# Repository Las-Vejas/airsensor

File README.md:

# かぜ (kaze)

A surrounding sensor that measures a bunch of things!
Heres a list of what it can measure:
 - Temperature (BME680)
 - Humidity (BME680)
 - Pressure (BME680)
 - CO<sub>2</sub> (BME680) (therefore AQI too)
 - lux (TSL2561)
 - and a couple more...

It is powered by the ESP32-C6 module and supports IoT protocols like Zigbee, Wi-fi, Bluetooth and Thread.
The software (that I will eventually write) will be for ESPHome as its very easy to set up IoT and home devices that way with the help of Home Assistant.

The biggest cost for this project would be the BME680 sensor as it costs about 10$

## Images

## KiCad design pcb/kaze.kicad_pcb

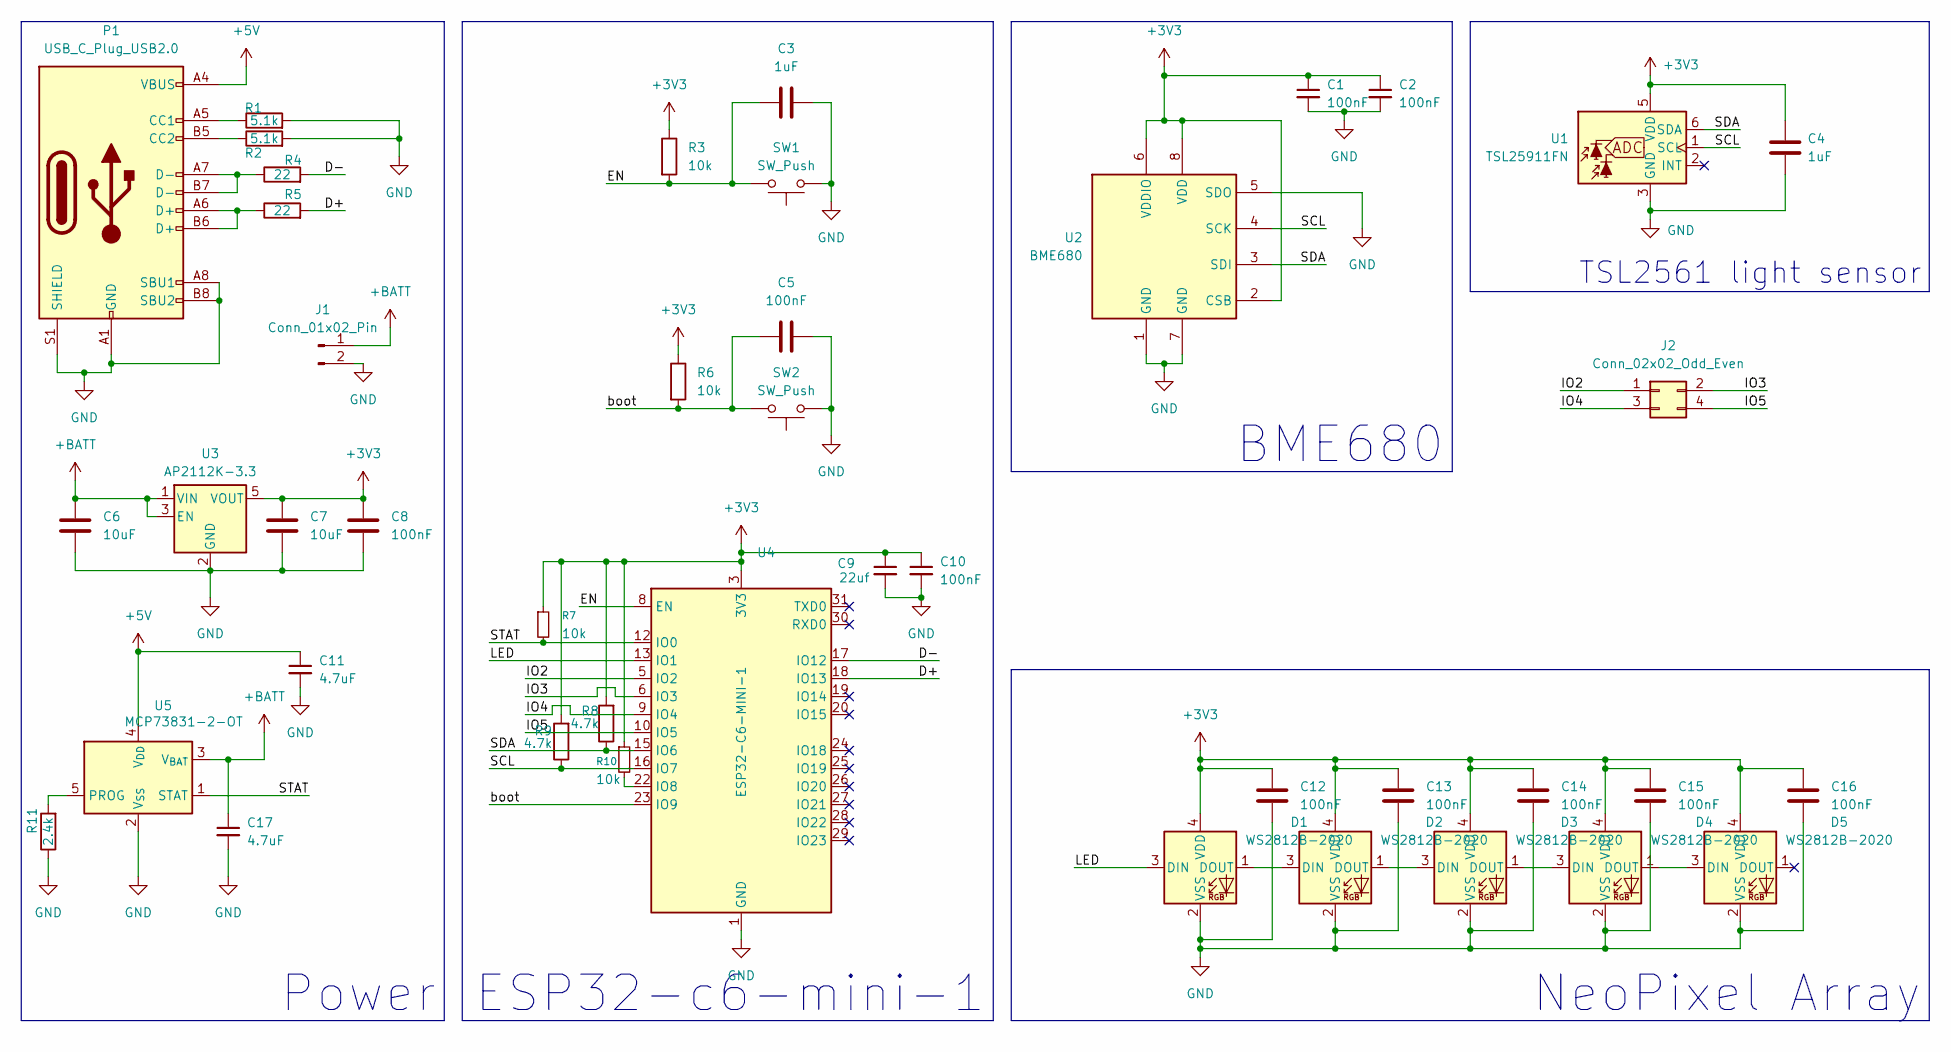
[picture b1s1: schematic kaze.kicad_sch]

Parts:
C1, C2, C5, C8, C10, C12, C13, C14, C15, C16: 100nF; C_0402_1005Metric
C3, C4: 1uF; C_0402_1005Metric
C6, C7: 10uF; C_0402_1005Metric
C9: 22uf; C_0402_1005Metric
C11, C17: 4.7uF; C_0402_1005Metric
D1, D2, D3, D4, D5: WS2812B-2020; LED_WS2812B-2020_PLCC4_2.0x2.0mm
J1: Conn_01x02_Pin; PinHeader_1x02_P1.00mm_Vertical
J2: Conn_02x02_Odd_Even; PinHeader_2x02_P1.00mm_Vertical
P1: USB_C_Plug_USB2.0; USB_C_Receptacle_GCT_USB4105-xx-A_16P_TopMnt_Horizontal
R1, R2: 5.1k; R_0402_1005Metric
R3, R6, R7, R10: 10k; R_0402_1005Metric
R4, R5: 22; R_0402_1005Metric
R8, R9: 4.7k; R_0402_1005Metric
R11: 2.4k; R_0402_1005Metric
SW1, SW2: SW_Push; SW_Push_SPST_NO_Alps_SKRK
U1: TSL25911FN; AMS_TSL25911FN
U2: BME680; Bosch_LGA-8_3x3mm_P0.8mm_ClockwisePinNumbering
U3: AP2112K-3.3; SOT-23-5
U4: ESP32-C6-MINI-1
U5: MCP73831-2-OT; SOT-23-5

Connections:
+3V3: C1.1, C2.1, C4.1, C7.1, C8.1, C9.1, C10.1, C12.1, C13.1, C14.1, C15.1, C16.1, D1.4 (VDD), D2.4 (VDD), D3.4 (VDD), D4.4 (VDD), D5.4 (VDD), R3.1, R6.1, R7.1, R8.2, R9.2, R10.1, U1.5 (VDD), U2.2 (CSB), U2.6 (VDDIO), U2.8 (VDD), U3.5 (VOUT), U4.3 (3V3)
+5V: C11.1, P1.A4 (VBUS), P1.A9 (VBUS), P1.B4 (VBUS), P1.B9 (VBUS), U5.4 (V_{DD})
+BATT: C6.1, C17.1, J1.1, U3.1 (VIN), U3.3 (EN), U5.3 (V_{BAT})
/D+: R5.2, U4.18 (IO13)
/D-: R4.2, U4.17 (IO12)
/EN: C3.1, R3.2, SW1.2, U4.8 (EN)
/IO2: J2.1, U4.5 (IO2)
/IO3: J2.2, U4.6 (IO3)
/IO4: J2.3, U4.9 (IO4)
/IO5: J2.4, U4.10 (IO5)
/LED: D1.3 (DIN), U4.13 (IO1)
/SCL: R9.1, U1.1 (SCL), U2.4 (SCK), U4.16 (IO7)
/SDA: R8.1, U1.6 (SDA), U2.3 (SDI), U4.15 (IO6)
/STAT: R7.2, U4.12 (IO0), U5.1 (STAT)
/boot: C5.1, R6.2, SW2.2, U4.23 (IO9)
GND: C1.2, C2.2, C3.2, C4.2, C5.2, C6.2, C7.2, C8.2, C9.2, C10.2, C11.2, C12.2, C13.2, C14.2, C15.2, C16.2, C17.2, D1.2 (VSS), D2.2 (VSS), D3.2 (VSS), D4.2 (VSS), D5.2 (VSS), J1.2, P1.A1 (GND), P1.A8 (SBU1), P1.A12 (GND), P1.B1 (GND), P1.B8 (SBU2), P1.B12 (GND), P1.S1 (SHIELD), R1.2, R2.2, R11.1, SW1.1, SW2.1, U1.3 (GND), U2.1 (GND), U2.5 (SDO), U2.7 (GND), U3.2 (GND), U4.1 (GND), U4.2 (GND), U4.11 (GND), U4.14 (GND), U4.36 (GND), U4.37 (GND), U4.38 (GND), U4.39 (GND), U4.40 (GND), U4.41 (GND), U4.42 (GND), U4.43 (GND), U4.44 (GND), U4.45 (GND), U4.46 (GND), U4.47 (GND), U4.48 (GND), U4.49 (GND), U4.50 (GND), U4.51 (GND), U4.52 (GND), U4.53 (GND), U5.2 (V_{SS})
unnamed: D1.1 (DOUT), D2.3 (DIN)
unnamed: D2.1 (DOUT), D3.3 (DIN)
unnamed: D3.1 (DOUT), D4.3 (DIN)
unnamed: D4.1 (DOUT), D5.3 (DIN)
unnamed: P1.A5 (CC1), R1.1
unnamed: P1.B5 (CC2), R2.1
unnamed: P1.A6 (D+), P1.B6 (D+), R5.1
unnamed: P1.A7 (D-), P1.B7 (D-), R4.1
unnamed: R10.2, U4.22 (IO8)
unnamed: R11.2, U5.5 (PROG)

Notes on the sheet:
TSL2561 light sensor
ESP32-c6-mini-1
NeoPixel Array
Power
BME680

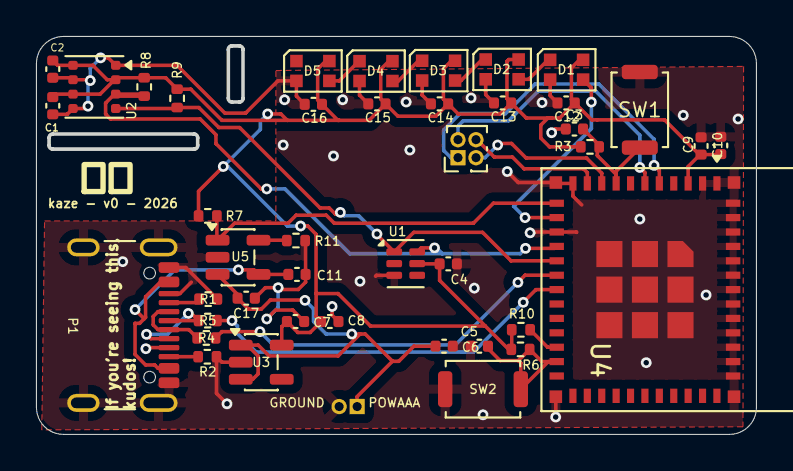
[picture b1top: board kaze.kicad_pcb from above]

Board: 2 copper layers, 39.9 x 22.0 mm, 43 parts (1 on the bottom side), 26 nets.

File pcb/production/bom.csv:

Designator,Footprint,Quantity,Value,LCSC Part #
"C1, C10, C12, C13, C14, C15, C16, C2, C5, C8",0402,10,100nF,
"C11, C17",0402,2,4.7uF,
"C3, C4",0402,2,1uF,
"C6, C7",0402,2,10uF,
C9,0402,1,22uf,
"D1, D2, D3, D4, D5",LED_WS2812B-2020_PLCC4_2.0x2.0mm,5,WS2812B-2020,
J1,PinHeader_1x02_P1.00mm_Vertical,1,Conn_01x02_Pin,
J2,PinHeader_2x02_P1.00mm_Vertical,1,Conn_02x02_Odd_Even,
P1,USB_C_Receptacle_GCT_USB4105-xx-A_16P_TopMnt_Horizontal,1,USB_C_Plug_USB2.0,
"R1, R2",0402,2,5.1k,
"R10, R3, R6, R7",0402,4,10k,
R11,0402,1,2.4k,
"R4, R5",0402,2,22,
"R8, R9",0402,2,4.7k,
"SW1, SW2",SW_Push_SPST_NO_Alps_SKRK,2,SW_Push,
U1,AMS_TSL25911FN,1,TSL25911FN,
U2,Bosch_LGA-8_3x3mm_P0.8mm_ClockwisePinNumbering,1,BME680,
U3,SOT-23-5,1,AP2112K-3.3,
U4,ESP32-C6-MINI-1,1,ESP32-C6-MINI-1,
U5,SOT-23-5,1,MCP73831-2-OT,

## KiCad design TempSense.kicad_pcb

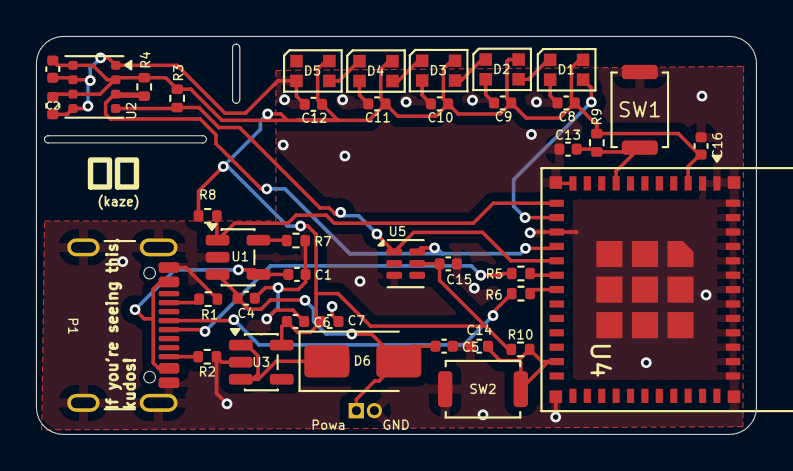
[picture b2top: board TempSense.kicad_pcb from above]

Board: 2 copper layers, 40.0 x 22.1 mm, 41 parts (0 on the bottom side), 22 nets.

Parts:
C1, C4: 4.7u; C_0402_1005Metric
C2, C3, C8, C9, C10, C11, C12, C16: 100nf; C_0402_1005Metric
C5: 10uf; C_0402_1005Metric
C6: 10u; C_0402_1005Metric
C7: 100n; C_0402_1005Metric
C13: 10uF; C_0402_1005Metric
C14: 100nF; C_0402_1005Metric
C15: 1uF; C_0402_1005Metric
D1, D2, D3, D4, D5: WS2812B-2020; LED_WS2812B-2020_PLCC4_2.0x2.0mm
D6: SS14; D_SMA
J1: Conn_01x02_Pin; PinHeader_2x01_P1.00mm_Vertical
P1: USB_C_Plug_USB2.0; USB_C_Receptacle_GCT_USB4105-xx-A_16P_TopMnt_Horizontal
R1, R2: 5.1k; R_0402_1005Metric
R3, R4: 4.7k; R_0402_1005Metric
R5, R6: 22; R_0402_1005Metric
R7: 2.4k; R_0402_1005Metric
R8, R9, R10: 10k; R_0402_1005Metric
SW1, SW2: SW_Push; SW_Push_SPST_NO_Alps_SKRK
U1: MCP73831-2-OT; SOT-23-5
U2: BME680; Bosch_LGA-8_3x3mm_P0.8mm_ClockwisePinNumbering
U3: AP2112K-3.3; SOT-23-5
U4: ESP32-C6-MINI-1
U5: TSL25911FN; AMS_TSL25911FN

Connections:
+3V3: C2.1, C3.1, C6.1, C7.1, C8.1, C9.1, C10.1, C11.1, C12.1, C15.1, C16.1, D1.4 (VDD), D2.4 (VDD), D3.4 (VDD), D4.4 (VDD), D5.4 (VDD), R3.2, R4.2, R8.1, R9.1, R10.1, U2.2 (CSB), U2.6 (VDDIO), U2.8 (VDD), U3.5 (VOUT), U4.3 (3V3), U5.5 (VDD)
+5V: C1.1, P1.A4 (VBUS), P1.A9 (VBUS), P1.B4 (VBUS), P1.B9 (VBUS), U1.4 (V_{DD})
+BATT: C4.1, C5.1, D6.2 (A), J1.1, U1.3 (V_{BAT})
/D+: R6.2, U4.18 (IO13)
/D-: R5.2, U4.17 (IO12)
/EN: C13.1, R9.2, SW1.2, U4.8 (EN)
/LED: D1.3 (DIN), U4.13 (IO1)
/SCL: R3.1, U2.4 (SCK), U4.16 (IO7), U5.1 (SCL)
/SDA: R4.1, U2.3 (SDI), U4.15 (IO6), U5.6 (SDA)
/STAT: R8.2, U1.1 (STAT), U4.12 (IO0)
/boot: C14.1, R10.2, SW2.2, U4.23 (IO9)
GND: C1.2, C2.2, C3.2, C4.2, C5.2, C6.2, C7.2, C8.2, C9.2, C10.2, C11.2, C12.2, C13.2, C14.2, C15.2, C16.2, D1.2 (VSS), D2.2 (VSS), D3.2 (VSS), D4.2 (VSS), D5.2 (VSS), J1.2, P1.A1 (GND), P1.A12 (GND), P1.B1 (GND), P1.B12 (GND), P1.S1 (SHIELD), R1.2, R2.2, R7.1, SW1.1, SW2.1, U1.2 (V_{SS}), U2.1 (GND), U2.5 (SDO), U2.7 (GND), U3.2 (GND), U4.1 (GND), U4.2 (GND), U4.11 (GND), U4.14 (GND), U4.36 (GND), U4.37 (GND), U4.38 (GND), U4.39 (GND), U4.40 (GND), U4.41 (GND), U4.42 (GND), U4.43 (GND), U4.44 (GND), U4.45 (GND), U4.46 (GND), U4.47 (GND), U4.48 (GND), U4.49 (GND), U4.50 (GND), U4.51 (GND), U4.52 (GND), U4.53 (GND), U5.3 (GND)
unnamed: D1.1 (DOUT), D2.3 (DIN)
unnamed: D2.1 (DOUT), D3.3 (DIN)
unnamed: D3.1 (DOUT), D4.3 (DIN)
unnamed: D4.1 (DOUT), D5.3 (DIN)
unnamed: D6.1 (K), U3.1 (VIN), U3.3 (EN)
unnamed: P1.A5 (CC), R1.1
unnamed: P1.A6 (D+), R6.1
unnamed: P1.A7 (D-), R5.1
unnamed: P1.B5 (VCONN), R2.1
unnamed: R7.2, U1.5 (PROG)

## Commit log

2026-01-09 Add Ko-fi funding link
    Added Ko-fi link for funding support.
2026-01-09 Change Ko-fi link to username format
    Updated Ko-fi username in FUNDING.yml
2026-01-09 stuffs
2026-01-10 almost finished
2026-01-14 pcb stuff
2026-01-17 bom update
2026-01-28 firmware
2026-01-28 gerbers
